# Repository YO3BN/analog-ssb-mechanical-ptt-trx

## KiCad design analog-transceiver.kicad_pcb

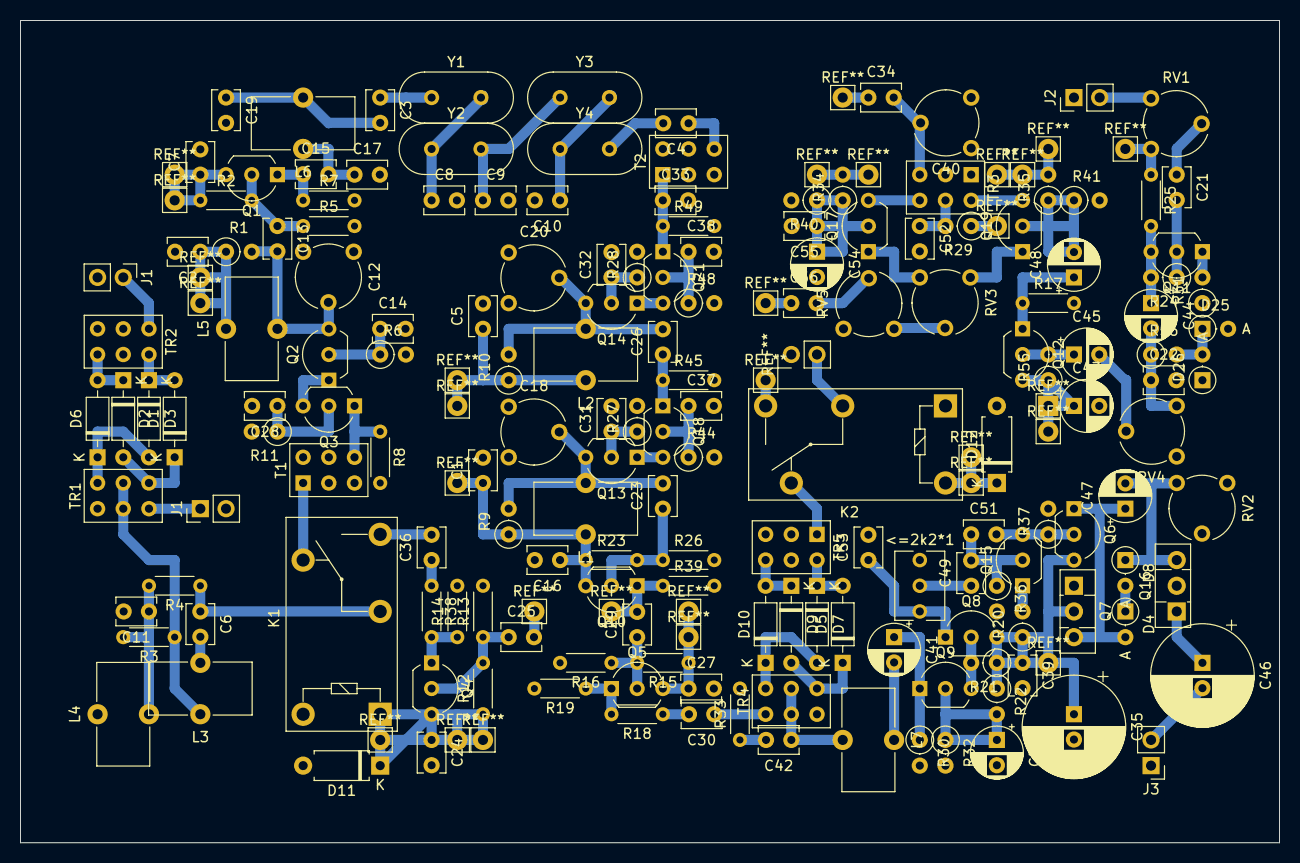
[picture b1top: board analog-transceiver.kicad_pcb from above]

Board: 2 copper layers, 124.5 x 81.3 mm, 167 parts (0 on the bottom side), 93 nets.

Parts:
<=2k2*1: 0; Potentiometer_Vishay_T73XW_Horizontal
C1, C2, C5, C7, C14, C15, C16, C24, C27, C28, C30, C31, C32, C36, C37, C38, C39, C56: 100n; C_Disc_D3.8mm_W2.6mm_P2.50mm
C3: 82pF (68-82pF); C_Disc_D3.8mm_W2.6mm_P2.50mm
C4: 68-82pF; C_Disc_D3.8mm_W2.6mm_P2.50mm
C6: 8.2p; C_Disc_D3.8mm_W2.6mm_P2.50mm
C8, C10: 100pF (82-120pF); C_Disc_D3.8mm_W2.6mm_P2.50mm
C9: 12opF (100-150pF); C_Disc_D3.8mm_W2.6mm_P2.50mm
C11: 10n; C_Disc_D3.8mm_W2.6mm_P2.50mm
C12, C18, C20: 25p; Potentiometer_Piher_PT-6-V_Vertical
C13, C23, C25, C26, C29, C34: 5p6; C_Disc_D3.8mm_W2.6mm_P2.50mm
C17: 2n*; C_Disc_D3.8mm_W2.6mm_P2.50mm
C19: 500p*; C_Disc_D3.8mm_W2.6mm_P2.50mm
C21, C49, C53: 680n; C_Disc_D3.8mm_W2.6mm_P2.50mm
C22: 47n*; C_Disc_D3.8mm_W2.6mm_P2.50mm
C33: ?; C_Disc_D3.8mm_W2.6mm_P2.50mm
C35: 470u; CP_Radial_D10.0mm_P2.50mm
C40: CTRIM; Potentiometer_Piher_PT-6-V_Vertical
C41: 10u; CP_Radial_D5.0mm_P2.50mm
C42: 330n; C_Disc_D3.8mm_W2.6mm_P2.50mm
C43, C44: 4.7u; CP_Radial_D5.0mm_P2.50mm
C45: 2.2u; CP_Radial_D5.0mm_P2.50mm
C46: 220u; CP_Radial_D10.0mm_P2.50mm
C47: 1u; CP_Radial_D5.0mm_P2.50mm
C48, C54: CP; CP_Radial_D5.0mm_P2.50mm
C50: 100u; CP_Radial_D5.0mm_P2.50mm
C51: 820p needed?; C_Disc_D3.8mm_W2.6mm_P2.50mm
C52, C55: C; C_Disc_D3.8mm_W2.6mm_P2.50mm
D1, D2, D3, D5, D6, D7, D9, D10: BAT41; D_DO-35_SOD27_P7.62mm_Horizontal
D4, D8: 1N4148; D_DO-35_SOD27_P2.54mm_Vertical_AnodeUp
D11, D12: 1n4007; D_A-405_P7.62mm_Horizontal
D25, D26: BAT41; D_DO-35_SOD27_P2.54mm_Vertical_AnodeUp
J1: LO; PinHeader_1x02_P2.54mm_Vertical
J1#2: BNC; PinHeader_1x02_P2.54mm_Vertical
J2: AF In; PinHeader_1x02_P2.54mm_Vertical
J3: AF Out; PinHeader_1x02_P2.54mm_Vertical
K1, K2: G5Q-1; Relay_SPDT_Omron-G5Q-1
L1, L2, L5: 12.6uH; L_Toroid_Vertical_L10.0mm_W5.0mm_P5.08mm
L3: 26.981u; L_Toroid_Vertical_L10.0mm_W5.0mm_P5.08mm
L4: 22.124n; L_Toroid_Vertical_L10.0mm_W5.0mm_P5.08mm
L6: 500n*; L_Toroid_Vertical_L10.0mm_W5.0mm_P5.08mm
L7: 820u; L_Toroid_Vertical_L10.0mm_W5.0mm_P5.08mm
Q1, Q2, Q4, Q5, Q6, Q8, Q9, Q10, Q11, Q12, Q13, Q14: 2N3904; TO-92_Inline_Wide
Q3, Q18, Q21: BF245A; TO-92_Inline_Wide
Q7: BD139; TO-126-3_Vertical
Q15: 2N3906; TO-92_Inline_Wide
Q16: BD140; TO-126-3_Vertical
Q17: 2n3904; TO-92_Inline_Wide
Q19: 2n2904; TO-92_Inline_Wide
R1, R9, R10: 6k8; R_Axial_DIN0207_L6.3mm_D2.5mm_P2.54mm_Vertical
R2: 100K; R_Axial_DIN0204_L3.6mm_D1.6mm_P5.08mm_Horizontal
R3, R4, R33: 50; R_Axial_DIN0204_L3.6mm_D1.6mm_P5.08mm_Horizontal
R5, R13, R16, R26: N/A; R_Axial_DIN0204_L3.6mm_D1.6mm_P5.08mm_Horizontal
R6, R21, R27, R28: 10k; R_Axial_DIN0207_L6.3mm_D2.5mm_P2.54mm_Vertical
R7: 390; R_Axial_DIN0204_L3.6mm_D1.6mm_P5.08mm_Horizontal
R8: 820; R_Axial_DIN0204_L3.6mm_D1.6mm_P5.08mm_Horizontal
R11, R44, R48: 330; R_Axial_DIN0207_L6.3mm_D2.5mm_P2.54mm_Vertical
R12, R15, R23: 180k; R_Axial_DIN0204_L3.6mm_D1.6mm_P5.08mm_Horizontal
R14, R17, R19, R39: 1k; R_Axial_DIN0204_L3.6mm_D1.6mm_P5.08mm_Horizontal
R18, R38: 39; R_Axial_DIN0204_L3.6mm_D1.6mm_P5.08mm_Horizontal
R20, R31, R56: 220; R_Axial_DIN0207_L6.3mm_D2.5mm_P2.54mm_Vertical
R22: 15k; R_Axial_DIN0207_L6.3mm_D2.5mm_P2.54mm_Vertical
R24, R36: 330k; R_Axial_DIN0207_L6.3mm_D2.5mm_P2.54mm_Vertical
R25: 2k2; R_Axial_DIN0204_L3.6mm_D1.6mm_P5.08mm_Horizontal
R29: 470; R_Axial_DIN0207_L6.3mm_D2.5mm_P2.54mm_Vertical
R30: 2k7; R_Axial_DIN0207_L6.3mm_D2.5mm_P2.54mm_Vertical
R32: 3.3k; R_Axial_DIN0207_L6.3mm_D2.5mm_P2.54mm_Vertical
R34, R35, R40, R41: 4k7; R_Axial_DIN0207_L6.3mm_D2.5mm_P2.54mm_Vertical
R37: 2k2; R_Axial_DIN0207_L6.3mm_D2.5mm_P2.54mm_Vertical
R45: 1M; R_Axial_DIN0204_L3.6mm_D1.6mm_P5.08mm_Horizontal
R49: 1M*; R_Axial_DIN0204_L3.6mm_D1.6mm_P5.08mm_Horizontal
R55: 180k; R_Axial_DIN0207_L6.3mm_D2.5mm_P2.54mm_Vertical
RV1: 10K; Potentiometer_Piher_PT-6-V_Vertical
RV2: 5k; Potentiometer_Piher_PT-6-V_Vertical
RV3: 100; Potentiometer_Piher_PT-6-V_Vertical
RV4: 10k; Potentiometer_Piher_PT-6-V_Vertical
RV5: 4k7; Potentiometer_Piher_PT-6-V_Vertical
T1: 2:8 Turns 43-material? iron powder?; SW_NKK_G1xJP
T2: iron powerder; SW_NKK_G1xJP
TR1, TR2, TR3: 3x3 43-binocular; SW_NKK_G1xJP
TR4, TR5: 3x3 43-toroid; SW_NKK_G1xJP
Y1, Y2, Y3, Y4: 10MHz; Crystal_HC49-U_Vertical

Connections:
+12V: C1.1, C5.1, C7.1, C16.1, L1.1, L2.1, Q1.3, Q10.3, R2.1, R9.1, R10.1, R23.1
+RX: C2.1, C27.1, C35.1, C39.1, L5.1, Q5.3, Q6.3, Q7.2, Q8.3, R1.1, R15.1, R20.1, R21.1, R22.1
+TX: C24.1, C43.1, D11.1, D12.1, K1.1, K2.5, Q4.3, Q12.3, R12.1, R25.1, R29.1, R34.2, R35.2, R55.1, RV1.1
GND: <=2k2*1.1, C1.2, C2.2, C5.2, C7.2, C8.2, C9.2, C10.2, C11.2, C12.1, C12.3, C14.2, C16.2, C17.2, C18.1, C18.3, C19.2, C20.1, C20.3, C22.2, C24.2, C27.2, C28.2, C31.2, C32.2, C33.2, C35.2, C37.2, C38.2, C39.2, C40.1, C40.3, C43.2, C50.2, C52.2, C53.2, C54.2, C55.2, D11.2, D12.2, D25.2, D26.1, J1.2, J1#2.2, J2.1, J3.1, K1.5, K2.1, L4.1, Q16.2, R5.2, R7.2, R8.2, R11.2, R13.2, R14.2, R16.2, R17.2, R19.2, R26.2, R30.2, R31.1, R32.2, R33.2, R37.2, R39.2, R40.2, R41.2, R44.2, R45.2, R48.2, R49.2, RV2.2, RV2.3, RV4.3, RV5.3, T1.2, T1.3, T2.2, T2.3, TR1.1, TR2.2, TR2.3, TR2.5, TR3.1, TR4.3, TR5.3, TR5.5
IFGain: R6.2, R27.2, R28.2
LO: J1.1, TR2.1
unnamed: <=2k2*1.2, C49.1
unnamed: <=2k2*1.3, C53.1, Q8.1
unnamed: C3.1, Y1.1
unnamed: C4.1, T2.4
unnamed: C4.2, Y4.2
unnamed: C6.1, K1.2, R4.1
unnamed: C6.2, L3.2
unnamed: C8.1, Y1.2, Y2.1
unnamed: C9.1, Y2.2, Y3.1
unnamed: C10.1, Y3.2, Y4.1
unnamed: C11.1, L4.2, R3.2, R4.2
unnamed: C12.2, C13.2, L5.2, Q2.3, R1.2
unnamed: C13.1, C34.1, Q1.2, R2.2, R5.1
unnamed: C14.1, Q2.2, R6.1
unnamed: C15.1, Q1.1, R7.1
unnamed: C15.2, C17.1, L6.1
unnamed: C18.2, C23.2, L1.2, Q13.3, R9.2
unnamed: C3.2, C19.1, L6.2
unnamed: C20.2, C26.2, L2.2, Q14.3, R10.2
unnamed: C21.1, RV1.2
unnamed: C21.2, Q11.2, R24.1
unnamed: C22.1, C44.2, R56.1, RV4.1
unnamed: C23.1, Q10.2, R23.2, R26.1
unnamed: C25.1, Q4.2, R12.2, R13.1
unnamed: C25.2, C29.2, Q10.1, R39.1
unnamed: C26.1, Q18.1, R45.1
unnamed: C28.1, Q3.2, R11.1
unnamed: C29.1, Q5.2, R15.2, R16.1
unnamed: C30.1, TR4.1
unnamed: C30.2, R18.1
unnamed: C31.1, Q13.2, R27.1
unnamed: C32.1, Q14.2, R28.1
unnamed: C33.1, Q21.1, R49.1, T2.1
unnamed: C34.2, C40.2, TR3.3
unnamed: C36.1, R38.1
unnamed: C36.2, K1.3
unnamed: C37.1, Q18.2, R44.1
unnamed: C38.1, Q21.2, R48.1
unnamed: C41.1, Q9.1, R30.1
unnamed: C41.2, L7.1
unnamed: C42.1, L7.2, TR4.2, TR4.5
unnamed: C42.2, R33.1
unnamed: C44.1, Q11.3, R24.2, R25.2
unnamed: C45.1, Q12.2, R55.2
unnamed: C45.2, RV4.2
unnamed: C46.1, Q7.1, Q16.1, R36.2
unnamed: C46.2, J3.2
unnamed: C47.1, D4.2, Q6.1, Q7.3
unnamed: C47.2, D8.1, Q16.3, RV2.1
unnamed: C48.1, Q12.1, R17.1
unnamed: C48.2, Q19.2, R35.1, R41.1
unnamed: C49.2, C51.1, Q15.2, R36.1
unnamed: C50.1, Q9.2, R22.2, R32.1
unnamed: C51.2, Q6.2, Q15.3, R37.1
unnamed: C52.1, R29.2, TR3.5
unnamed: C54.1, C55.1, Q17.2, R34.1, R40.1
unnamed: C56.1, K2.3
unnamed: C56.2, RV5.2
unnamed: D1.1, D2.2, TR1.4
unnamed: D1.2, D3.1, TR2.6
unnamed: D2.1, D6.2, TR2.4
unnamed: D3.2, D6.1, TR1.6
unnamed: D4.1, D8.2
unnamed: D5.1, D9.2, TR4.6
unnamed: D5.2, D7.1, TR5.6
unnamed: D7.2, D10.1, TR4.4
unnamed: D9.1, D10.2, TR5.4
unnamed: D25.1, D26.2, R56.2
unnamed: J1#2.1, TR1.3
unnamed: J2.2, RV1.3
unnamed: K1.4, T1.1
unnamed: K2.4, TR5.1
unnamed: L3.1, R3.1, TR1.2, TR1.5
unnamed: Q2.1, Q3.3
unnamed: Q3.1, R8.1, T1.4
unnamed: Q4.1, R14.1, R38.2
unnamed: Q5.1, R18.2, R19.1
unnamed: Q8.2, Q9.3, R21.2
unnamed: Q11.1, R31.2
unnamed: Q13.1, Q18.3
unnamed: Q14.1, Q21.3
unnamed: Q15.1, R20.2
unnamed: Q17.1, RV3.1
unnamed: Q17.3, TR3.4
unnamed: Q19.1, RV3.3
unnamed: Q19.3, TR3.6
unnamed: RV3.2, RV5.1

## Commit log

2022-10-12 First commit.
2022-10-19 Added L and C values for 10.7Mhz@50ohm diplexer.
2022-10-19 Replaced first IF amplifier after diplexer. Changed matching network for IN and OUT of the IF filter. Removed first amplifier stage after the IF filter. Added audio diplexer after the BFO mixer.
2022-10-19 Added TODO file.
2022-10-26 Changed component values for Rx audio pre-amp. to match 50ohms without adapter circuit. Changed balance resistor values at BFO mixer.
2022-10-27 Removed one stage from audio amplifier since the pre-amp should provide enough gain.
2022-10-27 Reworked diplexer values for smooth transition at 10.7MHz.
2022-10-29 Added missing footprints for new components.
2022-12-15 New design + Rellay PTT + 1st Prototype v1.
2022-12-15 Added build notes into TODO file.
2023-01-08 Calculated and tested impedances for quartz filter - the values are correct now. Added buffer after quartz filter because jfet+bjt cascode changes its impedance with applied AGC voltage.
